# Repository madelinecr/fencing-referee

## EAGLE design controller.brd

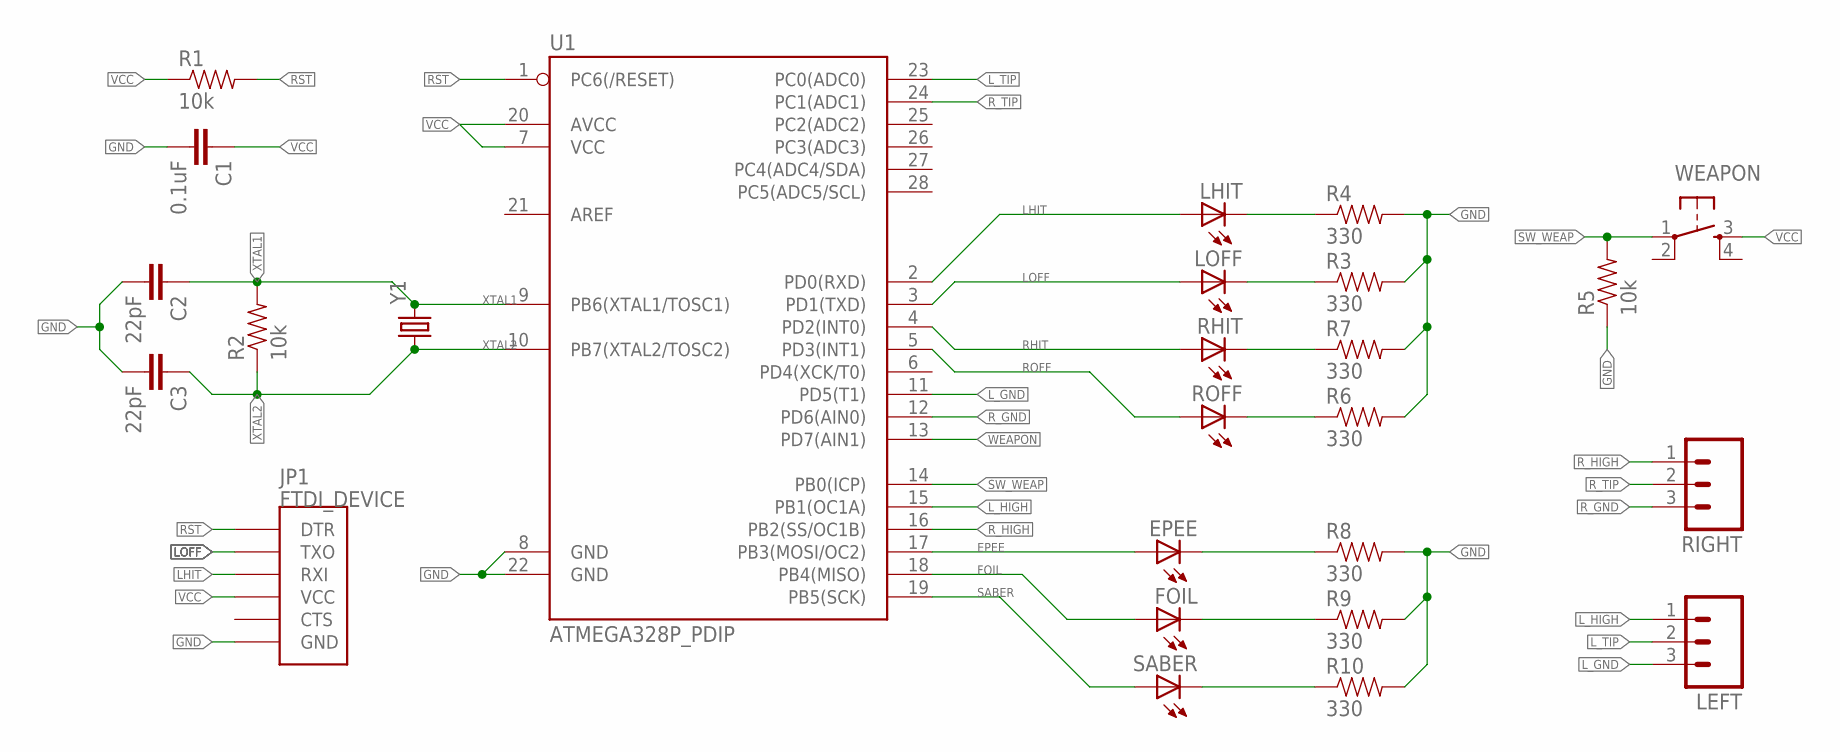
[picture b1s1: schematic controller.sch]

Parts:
C1: 0.1uF; CAP-PTH-SMALL-KIT
C2, C3: 22pF; CAP-PTH-SMALL-KIT
EPEE: LED5MM
FOIL: LED5MM
JP1: FTDI_DEVICE; FTDI_DEVICE_SIDE
LEFT: M03LOCK_LONGPADS; 1X03_LOCK_LONGPADS
LHIT: LED5MM
LOFF: LED5MM
R1, R2, R5: 10k; AXIAL-0.4
R3, R4, R6, R7, R8, R9, R10: 330; 0603-RES
RHIT: LED5MM
RIGHT: M03LOCK_LONGPADS; 1X03_LOCK_LONGPADS
ROFF: LED5MM
SABER: LED5MM
U1: ATMEGA328P_PDIP; DIL28-3
WEAPON: TAC_SWITCHPTH; TACTILE-PTH
Y1: CRYSTALHC49US; HC49US

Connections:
EPEE: EPEE.A, U1.17 (PB3(MOSI/OC2))
FOIL: FOIL.A, U1.18 (PB4(MISO))
GND: C1.2, C2.2, C3.2, JP1.P$6 (GND), R3.2, R4.2, R5.P$1 (1), R6.2, R7.2, R8.2, R9.2, R10.2, U1.8 (GND), U1.22 (GND)
LHIT: JP1.P$3 (RXI), LHIT.A, U1.2 (PD0(RXD))
LOFF: JP1.P$2 (TXO), LOFF.A, U1.3 (PD1(TXD))
L_GND: LEFT.3, U1.11 (PD5(T1))
L_HIGH: LEFT.1, U1.15 (PB1(OC1A))
L_TIP: LEFT.2, U1.23 (PC0(ADC0))
unnamed: LHIT.K (C), R4.1
unnamed: LOFF.K (C), R3.1
unnamed: R7.1, RHIT.K (C)
unnamed: R6.1, ROFF.K (C)
unnamed: FOIL.K (C), R9.1
unnamed: R10.1, SABER.K (C)
unnamed: EPEE.K (C), R8.1
RHIT: RHIT.A, U1.4 (PD2(INT0))
ROFF: ROFF.A, U1.5 (PD3(INT1))
RST: JP1.P$1 (DTR), R1.P$2 (2), U1.1 (PC6(/RESET))
R_GND: RIGHT.3, U1.12 (PD6(AIN0))
R_HIGH: RIGHT.1, U1.16 (PB2(SS/OC1B))
R_TIP: RIGHT.2, U1.24 (PC1(ADC1))
SABER: SABER.A, U1.19 (PB5(SCK))
SW_WEAP: R5.P$2 (2), U1.14 (PB0(ICP)), WEAPON.1
VCC: C1.1, JP1.P$4 (VCC), R1.P$1 (1), U1.7 (VCC), U1.20 (AVCC), WEAPON.3
WEAPON: U1.13 (PD7(AIN1))
XTAL1: C2.1, R2.P$2 (2), U1.9 (PB6(XTAL1/TOSC1)), Y1.2
XTAL2: C3.1, R2.P$1 (1), U1.10 (PB7(XTAL2/TOSC2)), Y1.1

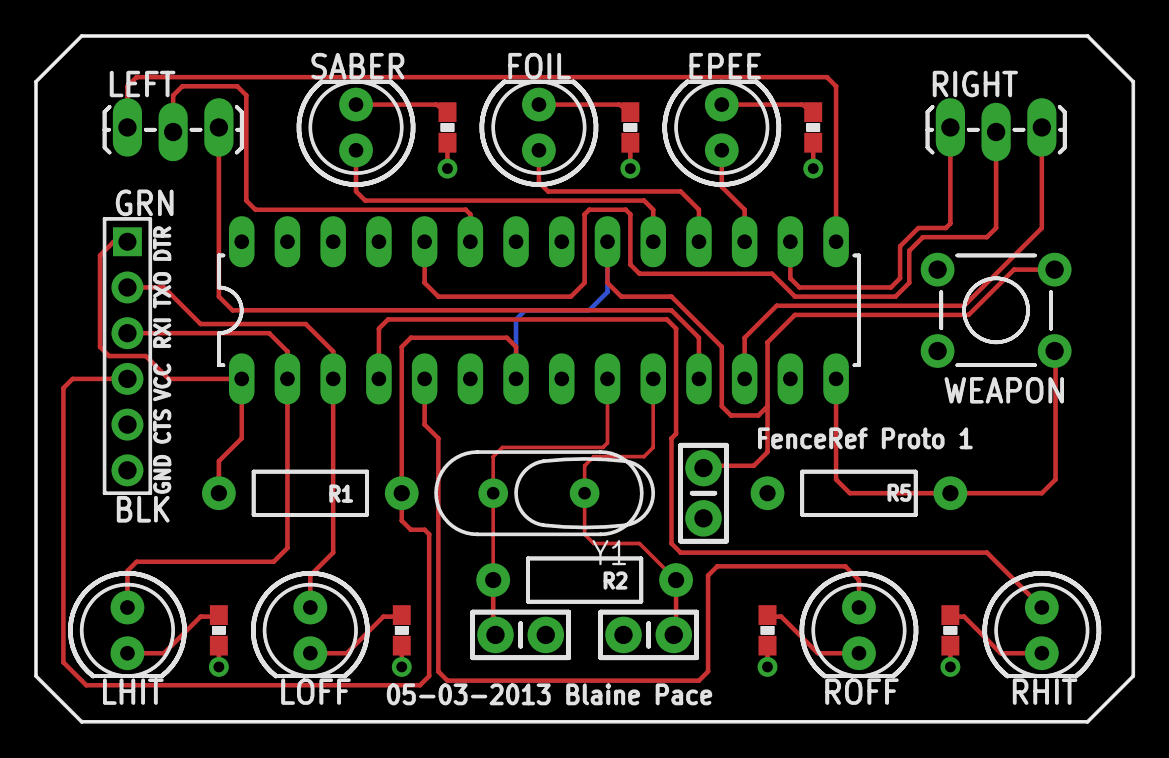
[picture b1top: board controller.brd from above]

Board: 2 copper layers, 61.0 x 38.1 mm, 26 parts (0 on the bottom side), 26 nets.

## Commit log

2013-02-28 Added barebones arduino project
2013-03-05 Added gitignroe file. Finished layout out board.
2013-03-05 Fixed part values and modified silkscreen
2013-03-05 Board passes OSHPark DRU
2013-03-05 Added OSHPark DRU and modified SFE CAM
2013-03-05 Ignored .ger and .xln files
2013-03-05 Replaced resonator with crystal and updated CAM job
2013-03-05 Finalized CAM setup
2013-03-05 Added cam files directory
2013-03-25 Added Arduino CMake project
2013-03-26 Mapped functions to pin numbers
2013-03-26 Mapped pins and tested analog functions
    Mapped LED, signal and measurement pins to variables. Added rudimentary analog
    voltage detection that will illuminate the left hit LED.

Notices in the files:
parts and their libraries:
SparkFun-DigitalIC: Licensing: CC v3.0 Share-Alike You are welcome to use this library for commercial purposes.
